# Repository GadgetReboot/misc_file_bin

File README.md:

# misc_file_bin
Random files that don't belong anywhere in particular for one-off archiving

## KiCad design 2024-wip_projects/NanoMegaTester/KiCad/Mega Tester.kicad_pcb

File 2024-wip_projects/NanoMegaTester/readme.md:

# 40 pin cable testing platform prototype
<br><br><BR><BR>
Prototype of 40 pin cable testing platform, driven by Arduino Nano.<br><br>
Likely going to update design to use a more powerful ESP32

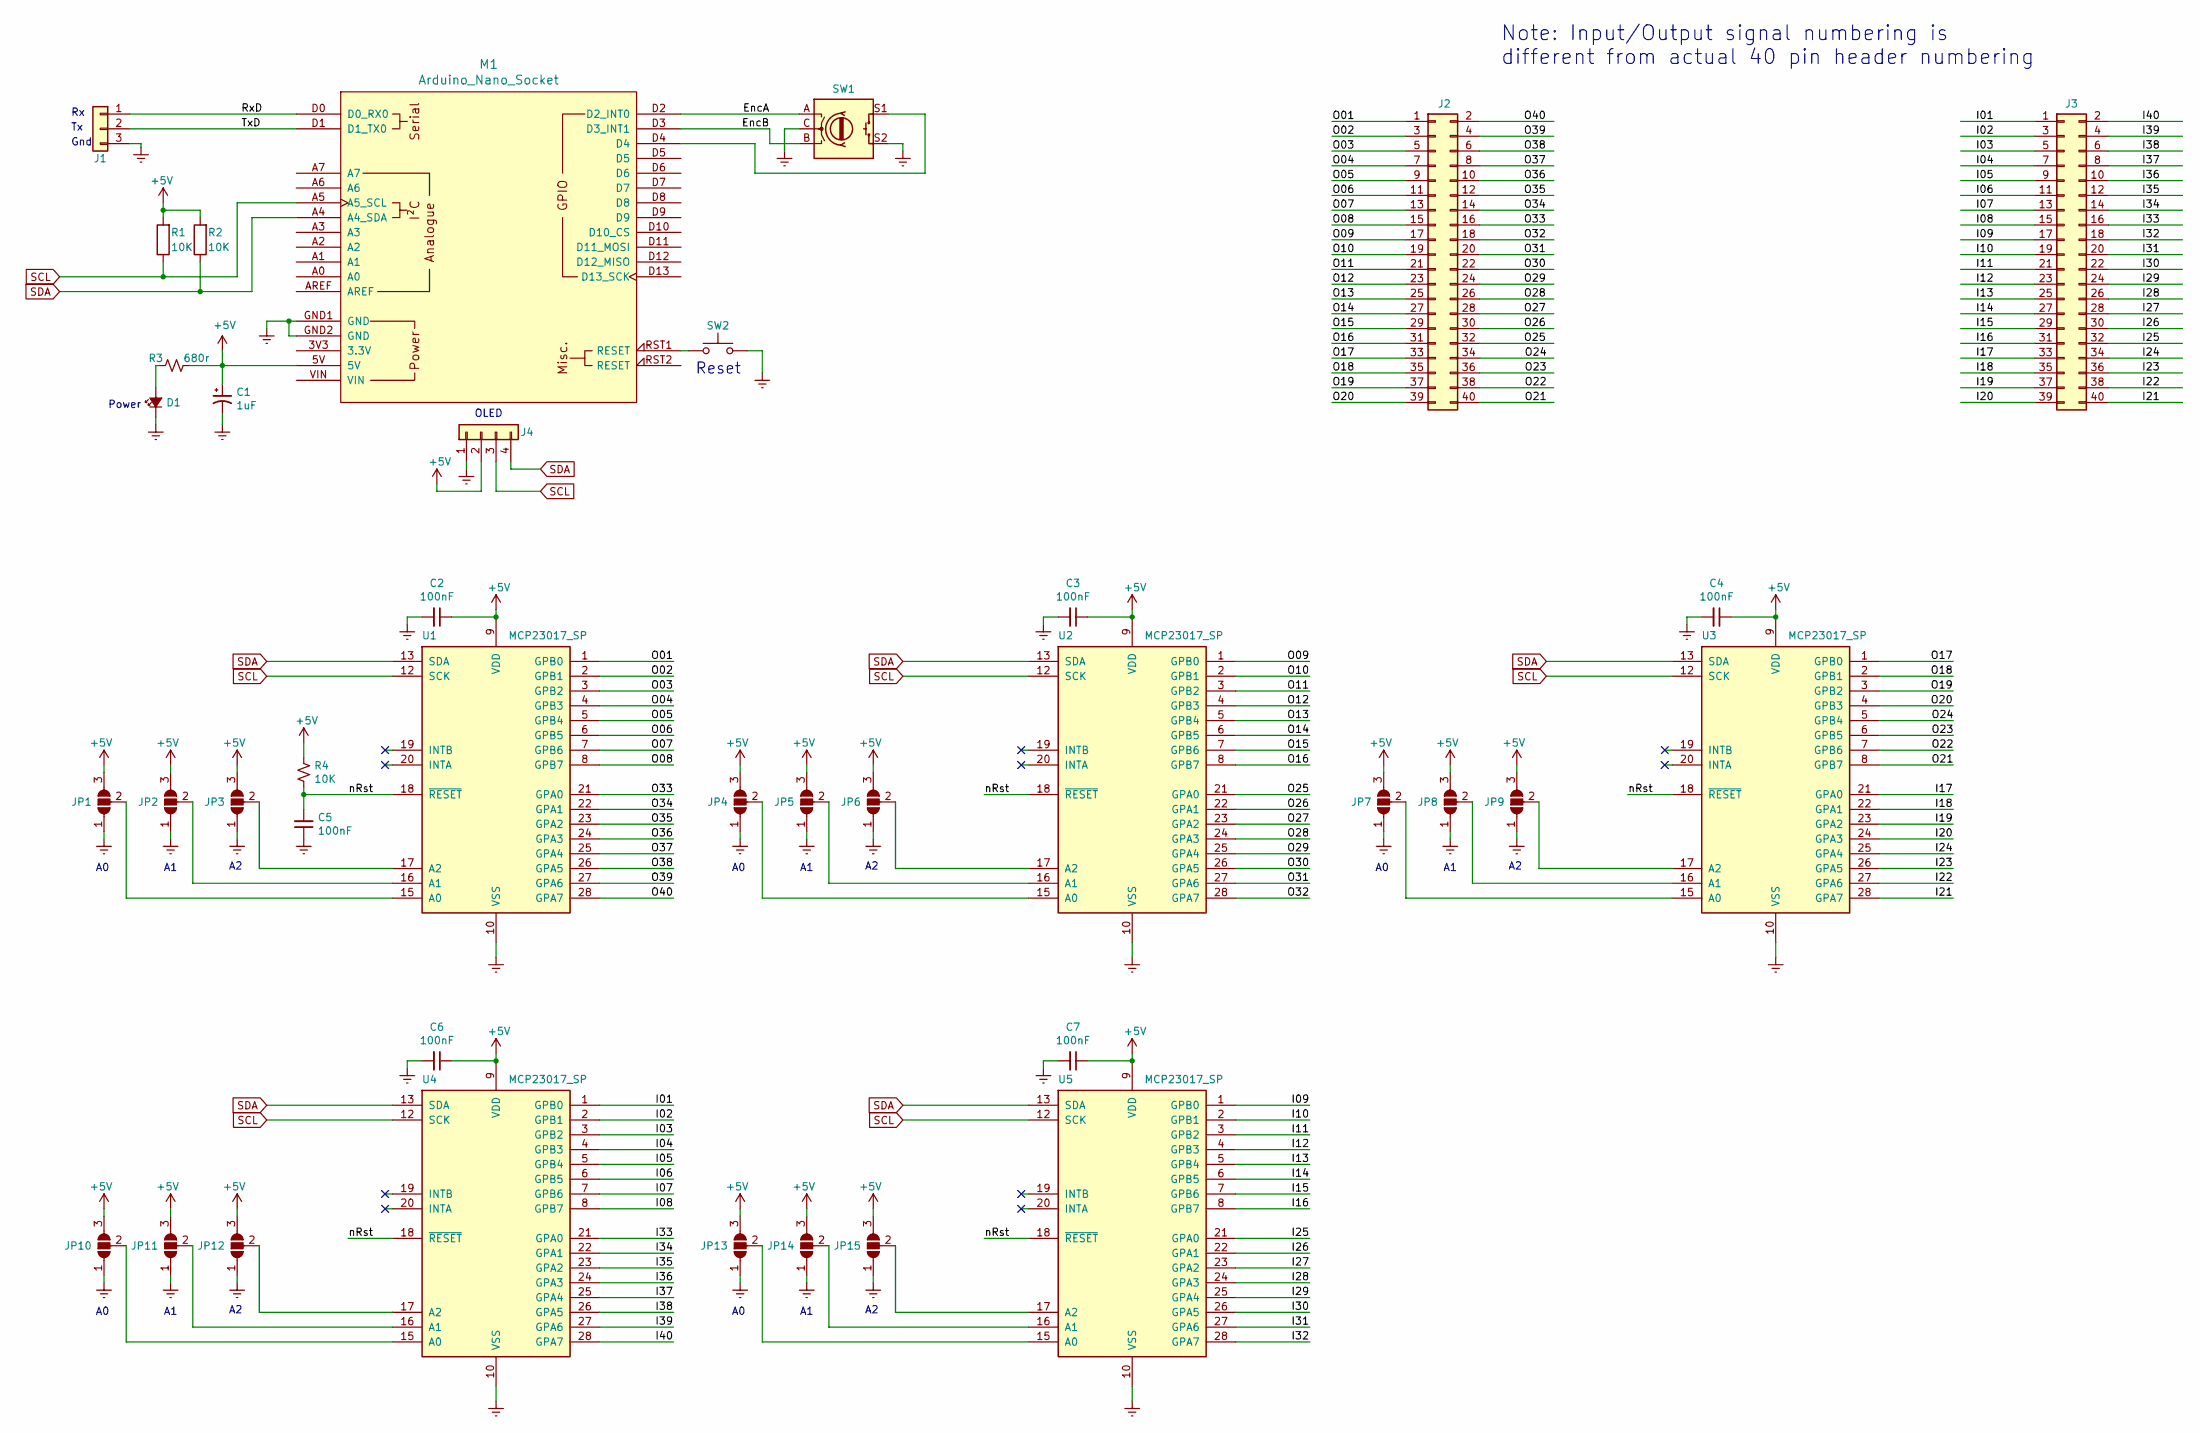
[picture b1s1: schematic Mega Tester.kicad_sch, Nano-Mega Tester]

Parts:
C1: 1uF; CP_Radial_D5.0mm_P2.50mm
C2, C3, C4, C5, C6, C7: 100nF; C_Disc_D3.8mm_W2.6mm_P2.50mm
D1: LED_Small_ALT; LED_D5.0mm
J1: UART; PinHeader_1x03_P2.54mm_Vertical
J2, J3: Conn_02x20_Odd_Even; PinHeader_2x20_P2.54mm_Vertical
J4: Conn_01x04; PinHeader_1x04_P2.54mm_Vertical
JP1, JP2, JP3, JP4, JP5, JP6, JP7, JP8, JP9, JP10, JP11, JP12, JP13, JP14, JP15: SolderJumper_3_Open; SolderJumper-3_P1.3mm_Open_RoundedPad1.0x1.5mm_NumberLabels
M1: Arduino_Nano_Socket
R1, R2, R4: 10K; R_Axial_DIN0207_L6.3mm_D2.5mm_P10.16mm_Horizontal
R3: 680r; R_Axial_DIN0207_L6.3mm_D2.5mm_P10.16mm_Horizontal
SW1: RotaryEncoder_Switch; RotaryEncoder_Alps_EC11E-Switch_Vertical_H20mm_CircularMoun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
SW2: SW_Push; SW_Tactile_Straight_KSA0Axx1LFTR
U1, U2, U3, U4, U5: MCP23017_SP; DIP-28_W7.62mm

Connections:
+5V: C1.1, C2.1, C3.1, C4.1, C6.1, C7.1, J4.2, JP1.3 (B), JP2.3 (B), JP3.3 (B), JP4.3 (B), JP5.3 (B), JP6.3 (B), JP7.3 (B), JP8.3 (B), JP9.3 (B), JP10.3 (B), JP11.3 (B), JP12.3 (B), JP13.3 (B), JP14.3 (B), JP15.3 (B), M1.5V, R1.2, R2.2, R3.1, R4.1, U1.9 (VDD), U2.9 (VDD), U3.9 (VDD), U4.9 (VDD), U5.9 (VDD)
/EncA: M1.D2 (D2_INT0), SW1.A
/EncB: M1.D3 (D3_INT1), SW1.B
/I01: J3.1, U4.1 (GPB0)
/I02: J3.3, U4.2 (GPB1)
/I03: J3.5, U4.3 (GPB2)
/I04: J3.7, U4.4 (GPB3)
/I05: J3.9, U4.5 (GPB4)
/I06: J3.11, U4.6 (GPB5)
/I07: J3.13, U4.7 (GPB6)
/I08: J3.15, U4.8 (GPB7)
/I09: J3.17, U5.1 (GPB0)
/I10: J3.19, U5.2 (GPB1)
/I11: J3.21, U5.3 (GPB2)
/I12: J3.23, U5.4 (GPB3)
/I13: J3.25, U5.5 (GPB4)
/I14: J3.27, U5.6 (GPB5)
/I15: J3.29, U5.7 (GPB6)
/I16: J3.31, U5.8 (GPB7)
/I17: J3.33, U3.21 (GPA0)
/I18: J3.35, U3.22 (GPA1)
/I19: J3.37, U3.23 (GPA2)
/I20: J3.39, U3.24 (GPA3)
/I21: J3.40, U3.28 (GPA7)
/I22: J3.38, U3.27 (GPA6)
/I23: J3.36, U3.26 (GPA5)
/I24: J3.34, U3.25 (GPA4)
/I25: J3.32, U5.21 (GPA0)
/I26: J3.30, U5.22 (GPA1)
/I27: J3.28, U5.23 (GPA2)
/I28: J3.26, U5.24 (GPA3)
/I29: J3.24, U5.25 (GPA4)
/I30: J3.22, U5.26 (GPA5)
/I31: J3.20, U5.27 (GPA6)
/I32: J3.18, U5.28 (GPA7)
/I33: J3.16, U4.21 (GPA0)
/I34: J3.14, U4.22 (GPA1)
/I35: J3.12, U4.23 (GPA2)
/I36: J3.10, U4.24 (GPA3)
/I37: J3.8, U4.25 (GPA4)
/I38: J3.6, U4.26 (GPA5)
/I39: J3.4, U4.27 (GPA6)
/I40: J3.2, U4.28 (GPA7)
/O01: J2.1, U1.1 (GPB0)
/O02: J2.3, U1.2 (GPB1)
/O03: J2.5, U1.3 (GPB2)
/O04: J2.7, U1.4 (GPB3)
/O05: J2.9, U1.5 (GPB4)
/O06: J2.11, U1.6 (GPB5)
/O07: J2.13, U1.7 (GPB6)
/O08: J2.15, U1.8 (GPB7)
/O09: J2.17, U2.1 (GPB0)
/O10: J2.19, U2.2 (GPB1)
/O11: J2.21, U2.3 (GPB2)
/O12: J2.23, U2.4 (GPB3)
/O13: J2.25, U2.5 (GPB4)
/O14: J2.27, U2.6 (GPB5)
/O15: J2.29, U2.7 (GPB6)
/O16: J2.31, U2.8 (GPB7)
/O17: J2.33, U3.1 (GPB0)
/O18: J2.35, U3.2 (GPB1)
/O19: J2.37, U3.3 (GPB2)
/O20: J2.39, U3.4 (GPB3)
/O21: J2.40, U3.8 (GPB7)
/O22: J2.38, U3.7 (GPB6)
/O23: J2.36, U3.6 (GPB5)
/O24: J2.34, U3.5 (GPB4)
/O25: J2.32, U2.21 (GPA0)
/O26: J2.30, U2.22 (GPA1)
/O27: J2.28, U2.23 (GPA2)
/O28: J2.26, U2.24 (GPA3)
/O29: J2.24, U2.25 (GPA4)
/O30: J2.22, U2.26 (GPA5)
/O31: J2.20, U2.27 (GPA6)
/O32: J2.18, U2.28 (GPA7)
/O33: J2.16, U1.21 (GPA0)
/O34: J2.14, U1.22 (GPA1)
/O35: J2.12, U1.23 (GPA2)
/O36: J2.10, U1.24 (GPA3)
/O37: J2.8, U1.25 (GPA4)
/O38: J2.6, U1.26 (GPA5)
/O39: J2.4, U1.27 (GPA6)
/O40: J2.2, U1.28 (GPA7)
/RxD: J1.1, M1.D0 (D0_RX0)
/TxD: J1.2, M1.D1 (D1_TX0)
/nRst: C5.2, R4.2, U1.18 (~RESET), U2.18 (~RESET), U3.18 (~RESET), U4.18 (~RESET), U5.18 (~RESET)
GNDREF: C1.2, C2.2, C3.2, C4.2, C5.1, C6.2, C7.2, D1.1 (K), J1.3, J4.1, JP1.1 (A), JP2.1 (A), JP3.1 (A), JP4.1 (A), JP5.1 (A), JP6.1 (A), JP7.1 (A), JP8.1 (A), JP9.1 (A), JP10.1 (A), JP11.1 (A), JP12.1 (A), JP13.1 (A), JP14.1 (A), JP15.1 (A), M1.GND1 (GND), M1.GND2 (GND), SW1.C, SW1.S2, SW2.1, U1.10 (VSS), U2.10 (VSS), U3.10 (VSS), U4.10 (VSS), U5.10 (VSS)
unnamed: D1.2 (A), R3.2
unnamed: JP1.2 (C), U1.15 (A0)
unnamed: JP2.2 (C), U1.16 (A1)
unnamed: JP3.2 (C), U1.17 (A2)
unnamed: JP4.2 (C), U2.15 (A0)
unnamed: JP5.2 (C), U2.16 (A1)
unnamed: JP6.2 (C), U2.17 (A2)
unnamed: JP7.2 (C), U3.15 (A0)
unnamed: JP8.2 (C), U3.16 (A1)
unnamed: JP9.2 (C), U3.17 (A2)
unnamed: JP10.2 (C), U4.15 (A0)
unnamed: JP11.2 (C), U4.16 (A1)
unnamed: JP12.2 (C), U4.17 (A2)
unnamed: JP13.2 (C), U5.15 (A0)
unnamed: JP14.2 (C), U5.16 (A1)
unnamed: JP15.2 (C), U5.17 (A2)
unnamed: M1.D4, SW1.S1
unnamed: M1.RST1 (RESET), SW2.2
SCL: J4.3, M1.A5 (A5_SCL), R1.1, U1.12 (SCK), U2.12 (SCK), U3.12 (SCK), U4.12 (SCK), U5.12 (SCK)
SDA: J4.4, M1.A4 (A4_SDA), R2.1, U1.13 (SDA), U2.13 (SDA), U3.13 (SDA), U4.13 (SDA), U5.13 (SDA)

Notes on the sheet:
OLED
Reset
Power
Note: Input/Output signal numbering is different from actual 40 pin header numbering
Gnd

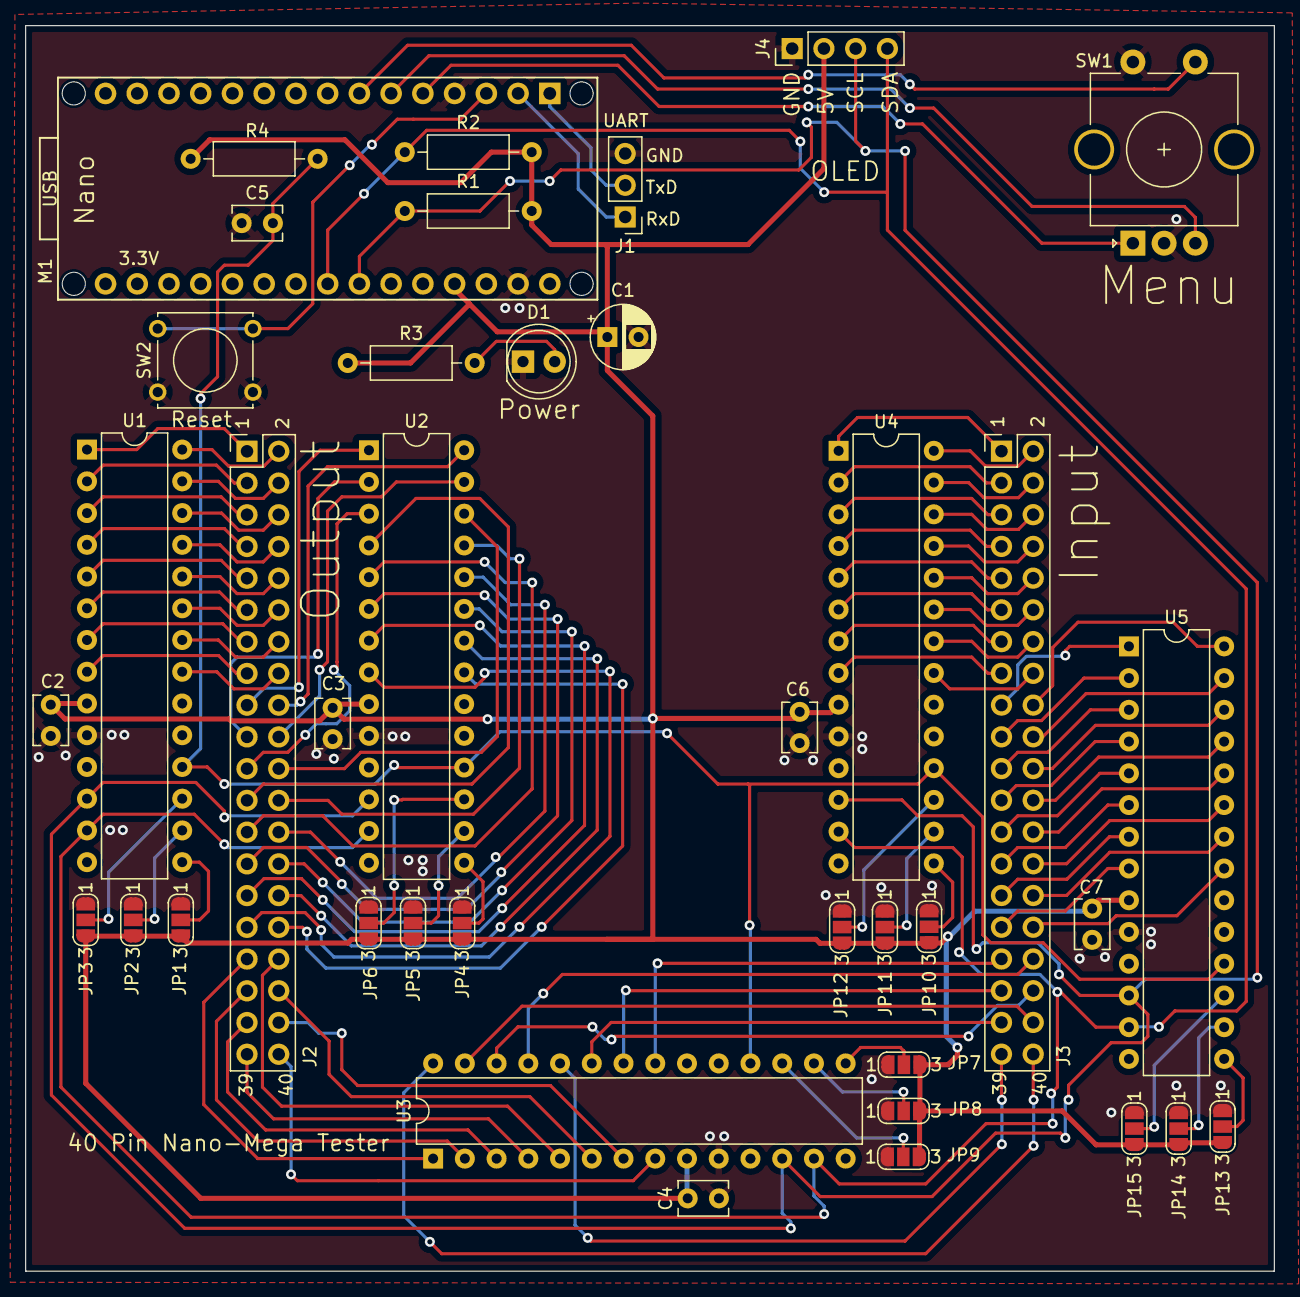
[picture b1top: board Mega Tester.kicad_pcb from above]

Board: 2 copper layers, 99.9 x 99.7 mm, 39 parts (0 on the bottom side), 107 nets.

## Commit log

2022-12-21 rename
2024-05-11 Create 2024-wip_projects
